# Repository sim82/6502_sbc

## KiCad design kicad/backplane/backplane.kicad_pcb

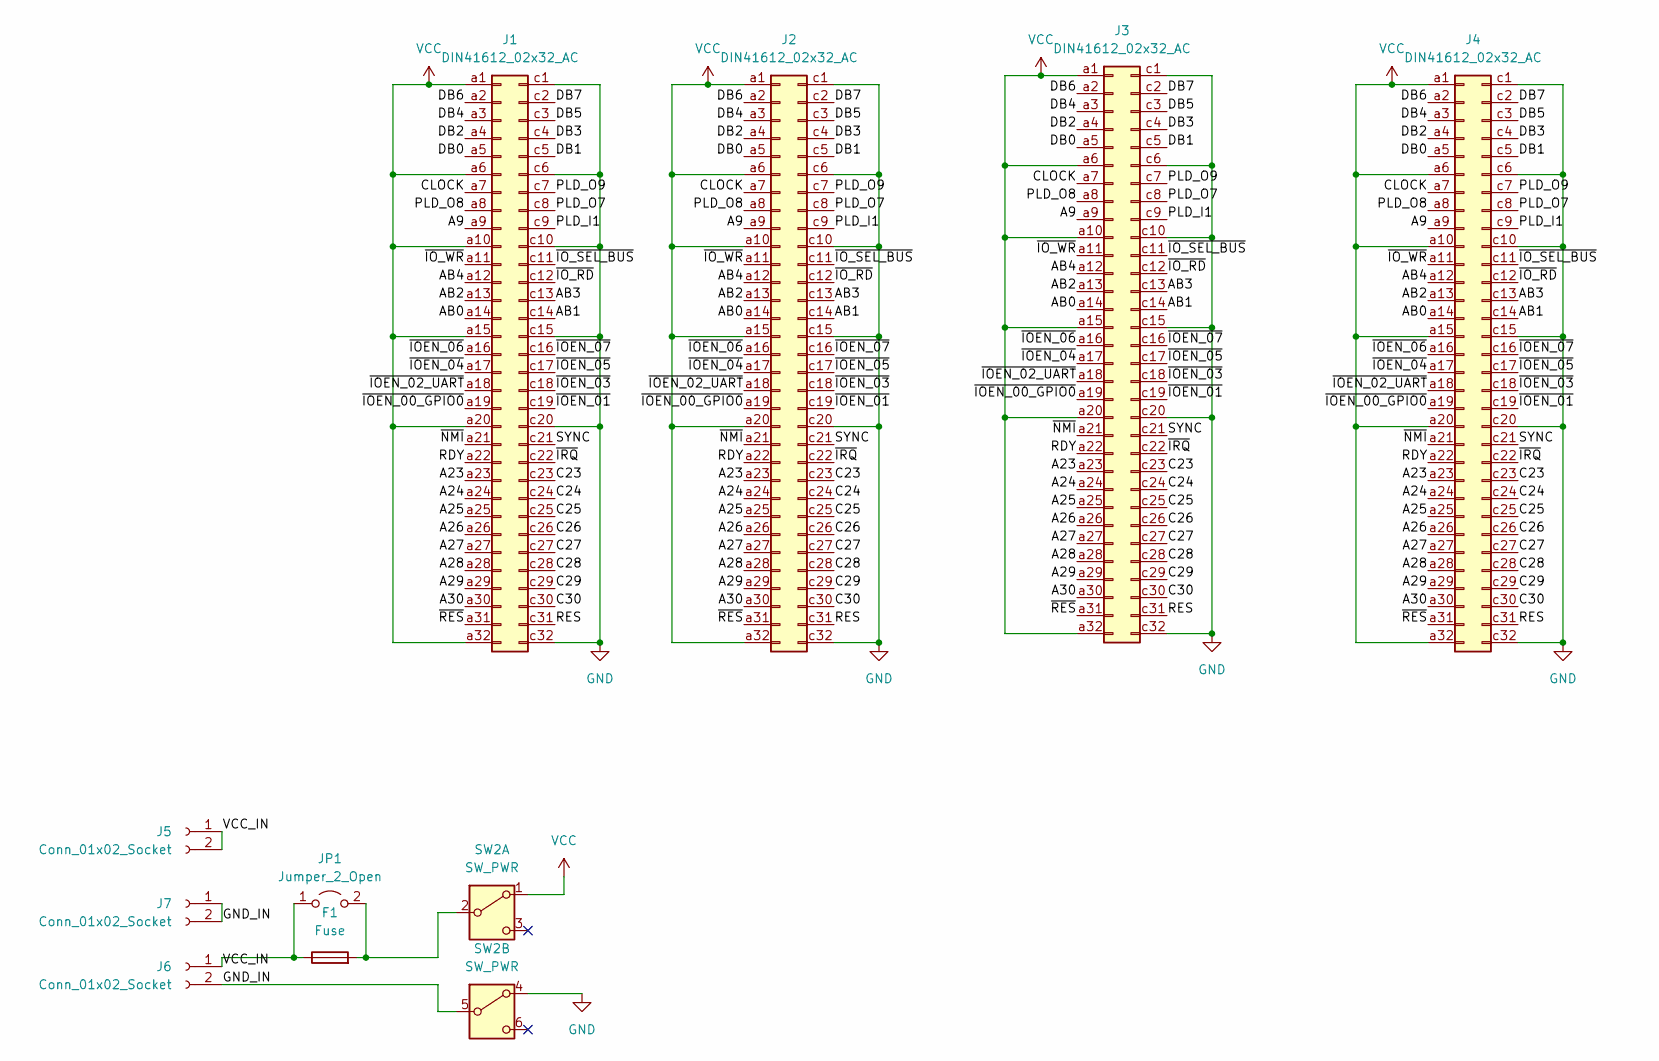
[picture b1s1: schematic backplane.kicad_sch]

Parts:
F1: Fuse; Fuseholder_Cylinder-5x20mm_Stelvio-Kontek_PTF78_Horizontal_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
J1, J2, J3, J4: DIN41612_02x32_AC; DIN41612_C_2x32_Female_Vertical_THT
J5, J6, J7: Conn_01x02_Socket; PinSocket_1x02_P2.54mm_Vertical
JP1: Jumper_2_Open; TestPoint_2Pads_Pitch2.54mm_Drill0.8mm
SW2: SW_PWR; 7x7DPDT

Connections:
/A9: J1.a9, J2.a9, J3.a9, J4.a9
/A23: J1.a23, J2.a23, J3.a23, J4.a23
/A24: J1.a24, J2.a24, J3.a24, J4.a24
/A25: J1.a25, J2.a25, J3.a25, J4.a25
/A26: J1.a26, J2.a26, J3.a26, J4.a26
/A27: J1.a27, J2.a27, J3.a27, J4.a27
/A28: J1.a28, J2.a28, J3.a28, J4.a28
/A29: J1.a29, J2.a29, J3.a29, J4.a29
/A30: J1.a30, J2.a30, J3.a30, J4.a30
/AB0: J1.a14, J2.a14, J3.a14, J4.a14
/AB1: J1.c14, J2.c14, J3.c14, J4.c14
/AB2: J1.a13, J2.a13, J3.a13, J4.a13
/AB3: J1.c13, J2.c13, J3.c13, J4.c13
/AB4: J1.a12, J2.a12, J3.a12, J4.a12
/C23: J1.c23, J2.c23, J3.c23, J4.c23
/C24: J1.c24, J2.c24, J3.c24, J4.c24
/C25: J1.c25, J2.c25, J3.c25, J4.c25
/C26: J1.c26, J2.c26, J3.c26, J4.c26
/C27: J1.c27, J2.c27, J3.c27, J4.c27
/C28: J1.c28, J2.c28, J3.c28, J4.c28
/C29: J1.c29, J2.c29, J3.c29, J4.c29
/C30: J1.c30, J2.c30, J3.c30, J4.c30
/CLOCK: J1.a7, J2.a7, J3.a7, J4.a7
/DB0: J1.a5, J2.a5, J3.a5, J4.a5
/DB1: J1.c5, J2.c5, J3.c5, J4.c5
/DB2: J1.a4, J2.a4, J3.a4, J4.a4
/DB3: J1.c4, J2.c4, J3.c4, J4.c4
/DB4: J1.a3, J2.a3, J3.a3, J4.a3
/DB5: J1.c3, J2.c3, J3.c3, J4.c3
/DB6: J1.a2, J2.a2, J3.a2, J4.a2
/DB7: J1.c2, J2.c2, J3.c2, J4.c2
/GND_IN: J6.2, J7.1, J7.2, SW2.5 (B)
/PLD_I1: J1.c9, J2.c9, J3.c9, J4.c9
/PLD_O7: J1.c8, J2.c8, J3.c8, J4.c8
/PLD_O8: J1.a8, J2.a8, J3.a8, J4.a8
/PLD_O9: J1.c7, J2.c7, J3.c7, J4.c7
/RDY: J1.a22, J2.a22, J3.a22, J4.a22
/RES: J1.c31, J2.c31, J3.c31, J4.c31
/SYNC: J1.c21, J2.c21, J3.c21, J4.c21
/VCC_IN: F1.1, J5.1, J5.2, J6.1, JP1.1 (A)
/~IOEN_00_GPIO0: J1.a19, J2.a19, J3.a19, J4.a19
/~IOEN_01: J1.c19, J2.c19, J3.c19, J4.c19
/~IOEN_02_UART: J1.a18, J2.a18, J3.a18, J4.a18
/~IOEN_03: J1.c18, J2.c18, J3.c18, J4.c18
/~IOEN_04: J1.a17, J2.a17, J3.a17, J4.a17
/~IOEN_05: J1.c17, J2.c17, J3.c17, J4.c17
/~IOEN_06: J1.a16, J2.a16, J3.a16, J4.a16
/~IOEN_07: J1.c16, J2.c16, J3.c16, J4.c16
/~IO_RD: J1.c12, J2.c12, J3.c12, J4.c12
/~IO_SEL_BUS: J1.c11, J2.c11, J3.c11, J4.c11
/~IO_WR: J1.a11, J2.a11, J3.a11, J4.a11
/~IRQ: J1.c22, J2.c22, J3.c22, J4.c22
/~NMI: J1.a21, J2.a21, J3.a21, J4.a21
/~RES: J1.a31, J2.a31, J3.a31, J4.a31
GND: J1.c1, J1.c6, J1.c10, J1.c15, J1.c20, J1.c32, J2.c1, J2.c6, J2.c10, J2.c15, J2.c20, J2.c32, J3.c1, J3.c6, J3.c10, J3.c15, J3.c20, J3.c32, J4.c1, J4.c6, J4.c10, J4.c15, J4.c20, J4.c32, SW2.4 (A)
unnamed: F1.2, JP1.2 (B), SW2.2 (B)
VCC: J1.a1, J1.a6, J1.a10, J1.a15, J1.a20, J1.a32, J2.a1, J2.a6, J2.a10, J2.a15, J2.a20, J2.a32, J3.a1, J3.a6, J3.a10, J3.a15, J3.a20, J3.a32, J4.a1, J4.a6, J4.a10, J4.a15, J4.a20, J4.a32, SW2.1 (A)

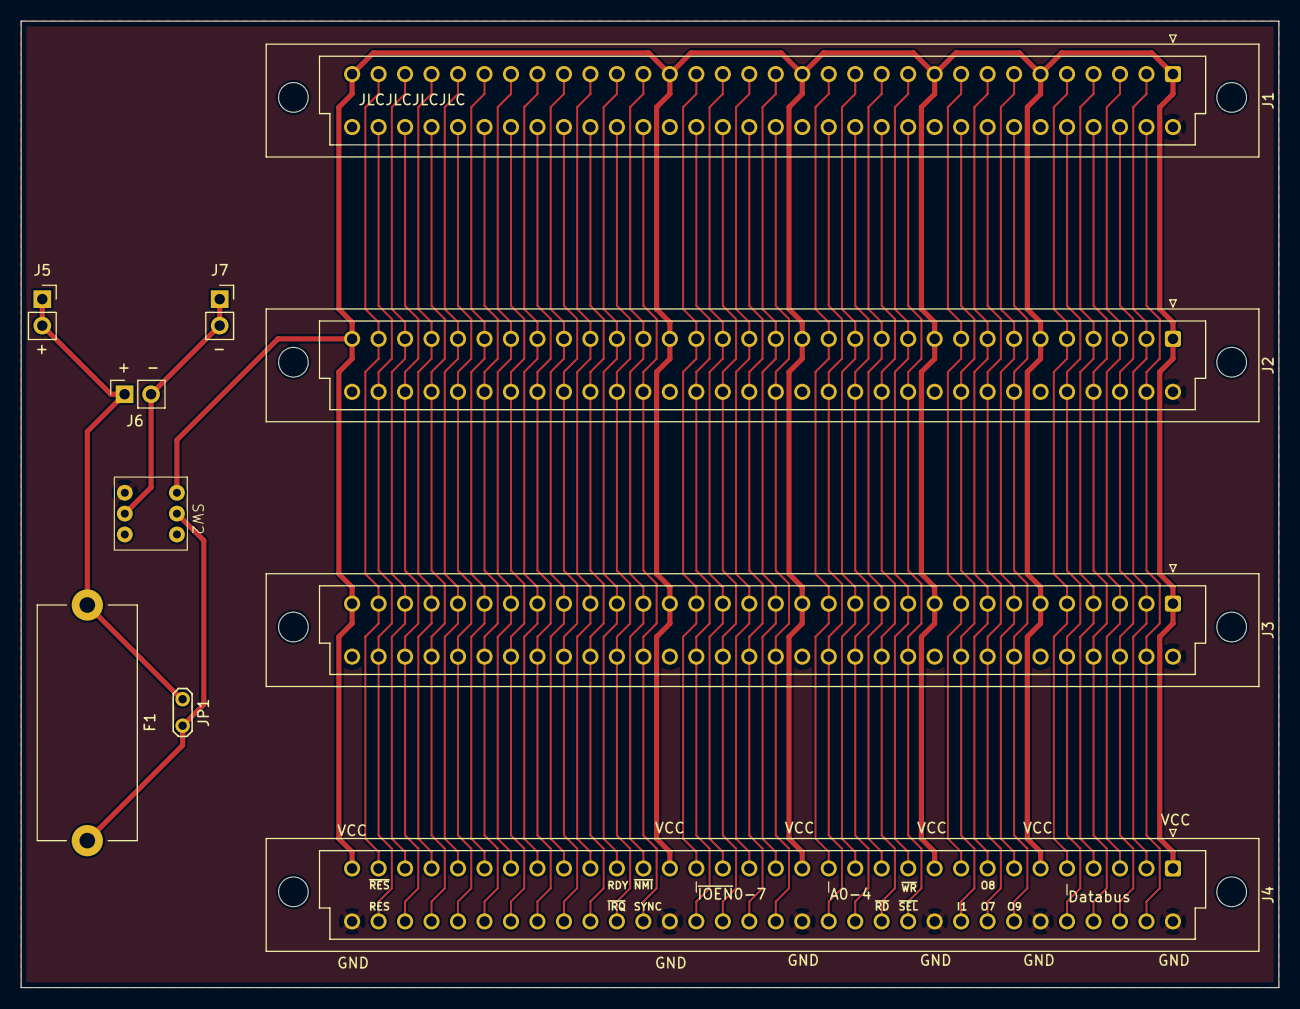
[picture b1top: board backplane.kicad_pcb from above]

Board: 2 copper layers, 120.6 x 92.7 mm, 10 parts (0 on the bottom side), 57 nets.

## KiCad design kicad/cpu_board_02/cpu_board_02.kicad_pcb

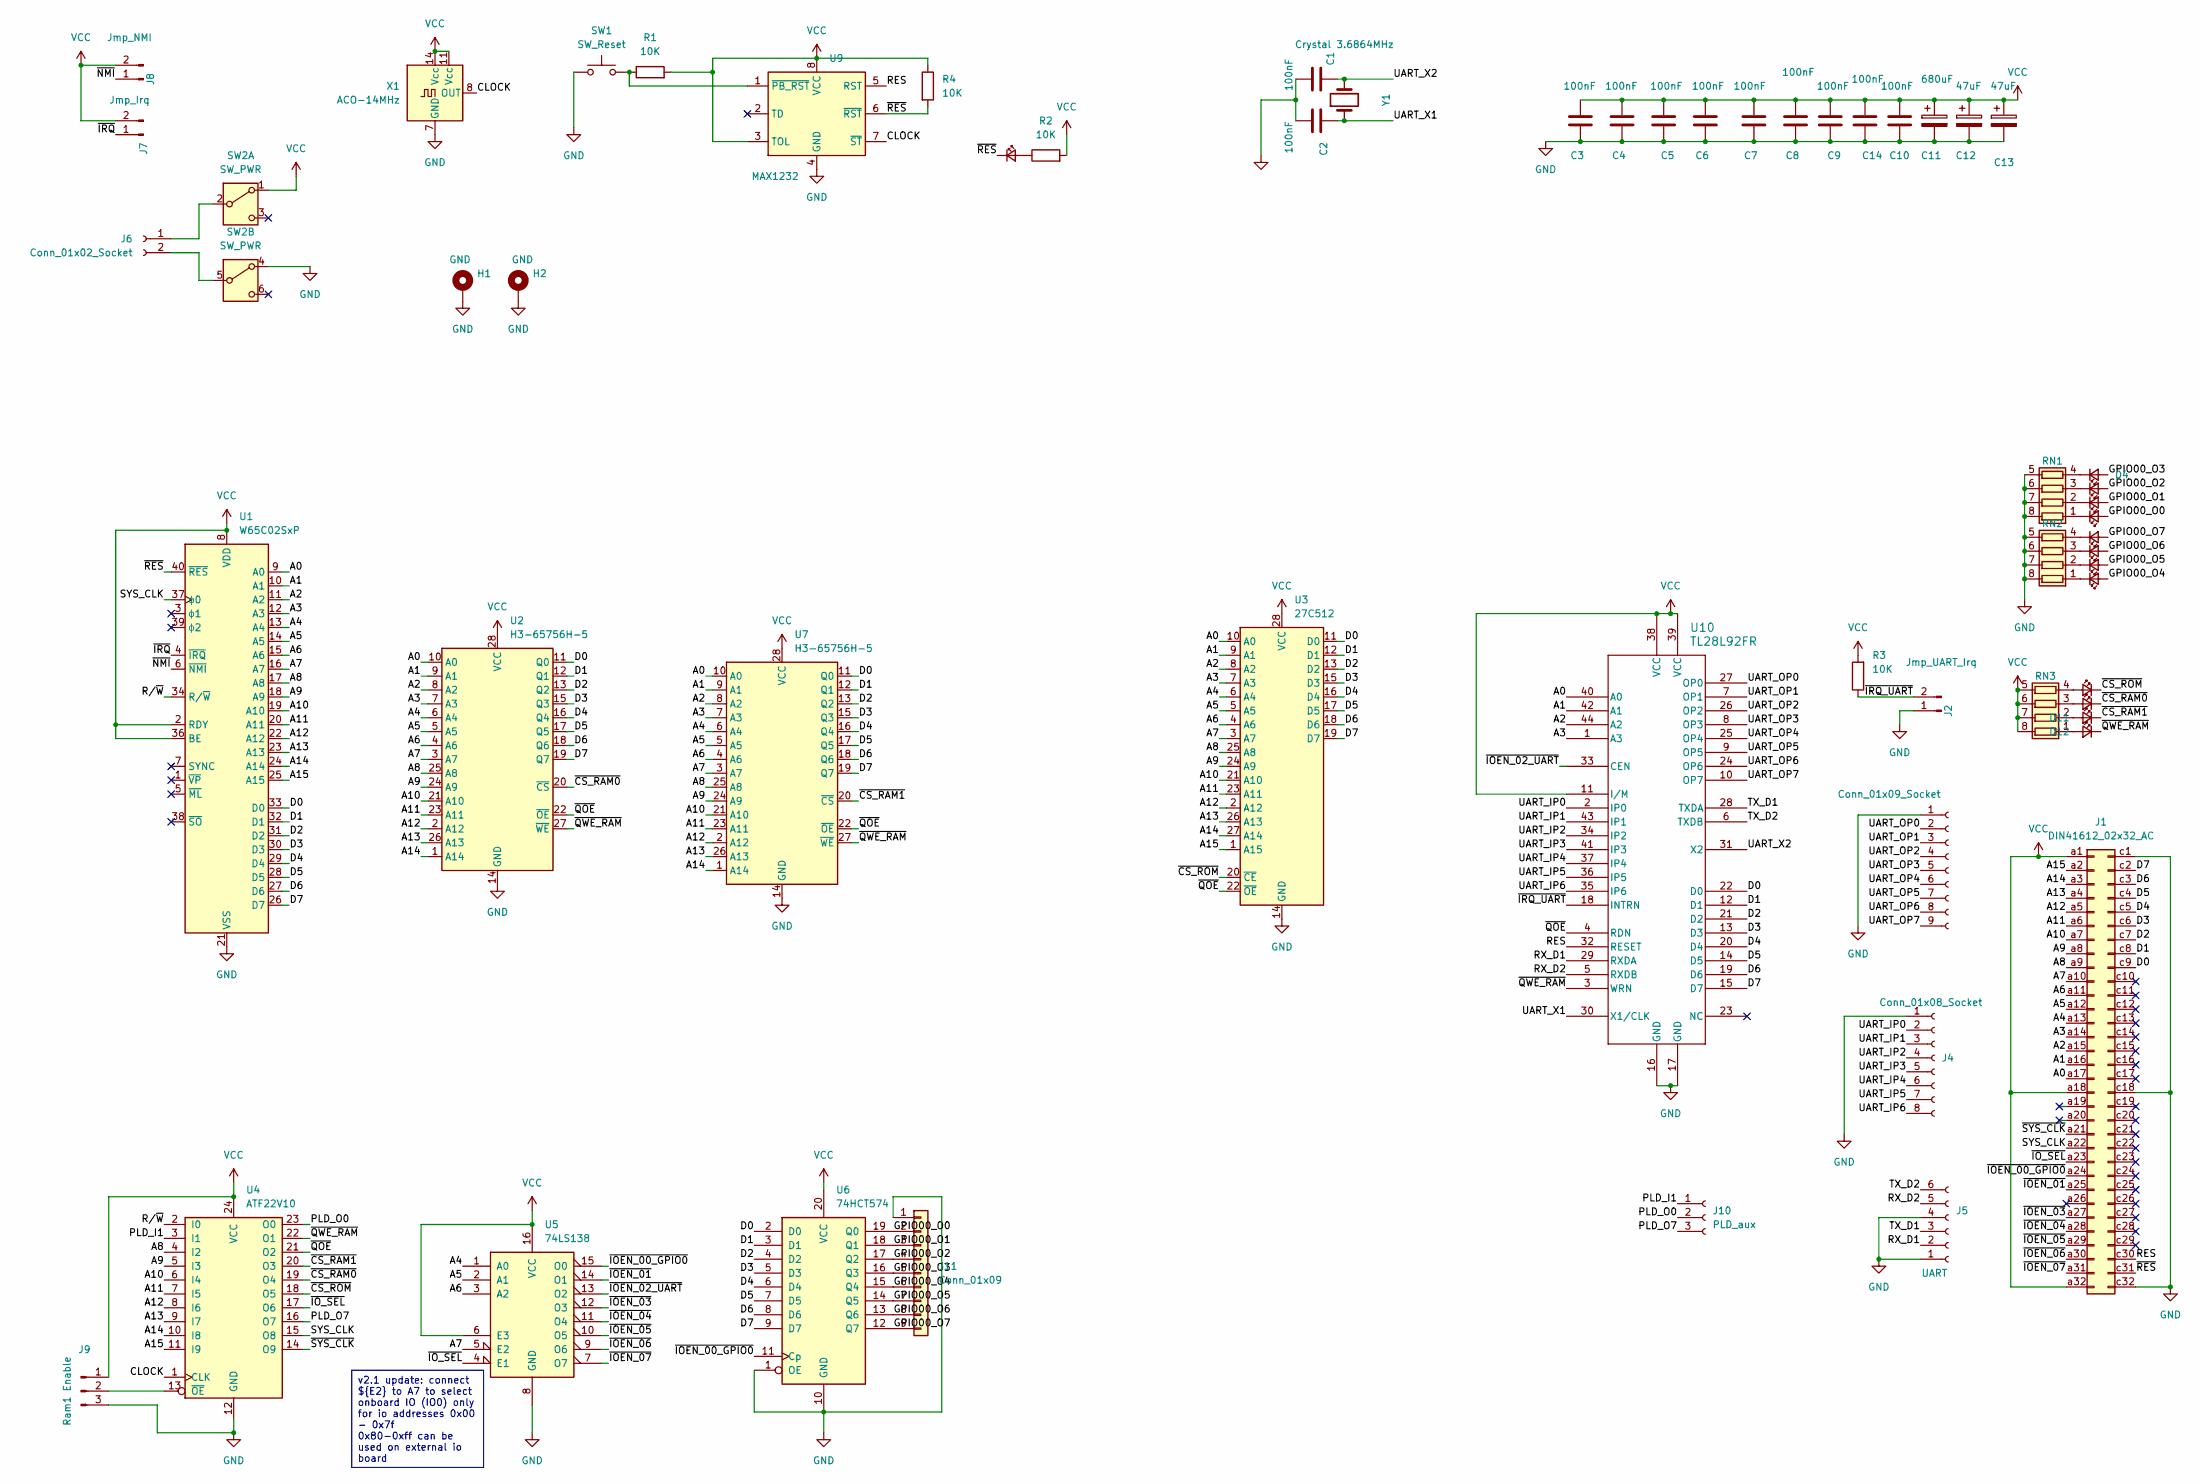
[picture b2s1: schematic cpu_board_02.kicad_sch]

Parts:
C1, C2: 100nF; C_Disc_D4.7mm_W2.5mm_P5.00mm
C3, C4, C5, C6, C7, C8, C9, C10, C14: 100nF; C_0805_2012Metric_Pad1.18x1.45mm_HandSolder
C11: 680uF; CP_Radial_D8.0mm_P5.00mm
C12, C13: 47uF; CP_Radial_D4.0mm_P2.00mm
D1, D2, D3, D4, D5, D6, D7, D8, D9, D10, D11, D12, D13: LED_Small; LED_0805_2012Metric_Pad1.15x1.40mm_HandSolder
H1, H2: GND; MountingHole_3.2mm_M3_DIN965_Pad
J1: DIN41612_02x32_AC; DIN41612_C_2x32_Male_Horizontal_THT
J2: Jmp_UART_Irq; PinSocket_1x02_P2.54mm_Vertical
J3: Conn_01x09_Socket; PinSocket_1x09_P2.54mm_Vertical
J4: Conn_01x08_Socket; PinSocket_1x08_P2.54mm_Vertical
J5: UART; PinSocket_1x06_P2.54mm_Vertical
J6: Conn_01x02_Socket; PinSocket_1x02_P2.54mm_Vertical
J7: Jmp_Irq; PinHeader_1x02_P2.54mm_Vertical
J8: Jmp_NMI; PinHeader_1x02_P2.54mm_Vertical
J9: Ram1 Enable; PinHeader_1x03_P2.54mm_Vertical
J10: PLD_aux; PinSocket_1x03_P2.54mm_Vertical
J11: Conn_01x09; PinSocket_1x09_P2.54mm_Vertical
R1, R2, R3, R4: 10K; R_0805_2012Metric_Pad1.20x1.40mm_HandSolder
RN1, RN2, RN3: R_Pack04; R_Array_Convex_4x0612
SW1: SW_Reset; SW_TH_Tactile_Omron_B3F-10xx
SW2: SW_PWR; 7x7DPDT
U1: W65C02SxP; DIP-40_W15.24mm_Socket
U2, U7: H3-65756H-5; DIP-28_W7.62mm_Socket
U3: 27C512; DIP-28_W15.24mm_Socket
U4: ATF22V10; DIP-24_W7.62mm_Socket
U5: 74LS138; DIP-16_W7.62mm_Socket
U6: 74HCT574; DIP-20_W7.62mm_Socket
U9: MAX1232; SO-8_3.9x4.9mm_P1.27mm
U10: TL28L92FR; MQFP-44_10x10mm_P0.8mm
X1: ACO-14MHz; DIP-14_W7.62mm
Y1: Crystal 3.6864MHz; Crystal_HC49-4H_Vertical

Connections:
/A0: J1.a17, U1.9 (A0), U2.10 (A0), U3.10 (A0), U7.10 (A0), U10.40 (A0)
/A1: J1.a16, U1.10 (A1), U2.9 (A1), U3.9 (A1), U7.9 (A1), U10.42 (A1)
/A2: J1.a15, U1.11 (A2), U2.8 (A2), U3.8 (A2), U7.8 (A2), U10.44 (A2)
/A3: J1.a14, U1.12 (A3), U2.7 (A3), U3.7 (A3), U7.7 (A3), U10.1 (A3)
/A4: J1.a13, U1.13 (A4), U2.6 (A4), U3.6 (A4), U5.1 (A0), U7.6 (A4)
/A5: J1.a12, U1.14 (A5), U2.5 (A5), U3.5 (A5), U5.2 (A1), U7.5 (A5)
/A6: J1.a11, U1.15 (A6), U2.4 (A6), U3.4 (A6), U5.3 (A2), U7.4 (A6)
/A7: J1.a10, U1.16 (A7), U2.3 (A7), U3.3 (A7), U5.5 (E2), U7.3 (A7)
/A8: J1.a9, U1.17 (A8), U2.25 (A8), U3.25 (A8), U4.4 (I2), U7.25 (A8)
/A9: J1.a8, U1.18 (A9), U2.24 (A9), U3.24 (A9), U4.5 (I3), U7.24 (A9)
/A10: J1.a7, U1.19 (A10), U2.21 (A10), U3.21 (A10), U4.6 (I4), U7.21 (A10)
/A11: J1.a6, U1.20 (A11), U2.23 (A11), U3.23 (A11), U4.7 (I5), U7.23 (A11)
/A12: J1.a5, U1.22 (A12), U2.2 (A12), U3.2 (A12), U4.8 (I6), U7.2 (A12)
/A13: J1.a4, U1.23 (A13), U2.26 (A13), U3.26 (A13), U4.9 (I7), U7.26 (A13)
/A14: J1.a3, U1.24 (A14), U2.1 (A14), U3.27 (A14), U4.10 (I8), U7.1 (A14)
/A15: J1.a2, U1.25 (A15), U3.1 (A15), U4.11 (I9)
/CLOCK: U4.1 (CLK), U9.7 (~ST), X1.8 (OUT)
/D0: J1.c9, U1.33 (D0), U2.11 (Q0), U3.11 (D0), U6.2 (D0), U7.11 (Q0), U10.22 (D0)
/D1: J1.c8, U1.32 (D1), U2.12 (Q1), U3.12 (D1), U6.3 (D1), U7.12 (Q1), U10.12 (D1)
/D2: J1.c7, U1.31 (D2), U2.13 (Q2), U3.13 (D2), U6.4 (D2), U7.13 (Q2), U10.21 (D2)
/D3: J1.c6, U1.30 (D3), U2.15 (Q3), U3.15 (D3), U6.5 (D3), U7.15 (Q3), U10.13 (D3)
/D4: J1.c5, U1.29 (D4), U2.16 (Q4), U3.16 (D4), U6.6 (D4), U7.16 (Q4), U10.20 (D4)
/D5: J1.c4, U1.28 (D5), U2.17 (Q5), U3.17 (D5), U6.7 (D5), U7.17 (Q5), U10.14 (D5)
/D6: J1.c3, U1.27 (D6), U2.18 (Q6), U3.18 (D6), U6.8 (D6), U7.18 (Q6), U10.19 (D6)
/D7: J1.c2, U1.26 (D7), U2.19 (Q7), U3.19 (D7), U6.9 (D7), U7.19 (Q7), U10.15 (D7)
/GPIO00_O0: D1.2 (A), J11.2, U6.19 (Q0)
/GPIO00_O1: D2.2 (A), J11.3, U6.18 (Q1)
/GPIO00_O2: D3.2 (A), J11.4, U6.17 (Q2)
/GPIO00_O3: D4.2 (A), J11.5, U6.16 (Q3)
/GPIO00_O4: D5.2 (A), J11.6, U6.15 (Q4)
/GPIO00_O5: D6.2 (A), J11.7, U6.14 (Q5)
/GPIO00_O6: D7.2 (A), J11.8, U6.13 (Q6)
/GPIO00_O7: D8.2 (A), J11.9, U6.12 (Q7)
/PLD_I1: J10.1, U4.3 (I1)
/PLD_O0: J10.2, U4.23 (O0)
/PLD_O7: J10.3, U4.16 (O7)
/RES: J1.c30, U9.5 (RST), U10.32 (RESET)
/RX_D1: J5.2, U10.29 (RXDA)
/RX_D2: J5.5, U10.5 (RXDB)
/R/~W: U1.34 (R/~W), U4.2 (I0)
/SYS_CLK: J1.a22, U1.37 (ϕ0), U4.15 (O8)
/TX_D1: J5.3, U10.28 (TXDA)
/TX_D2: J5.6, U10.6 (TXDB)
/UART_IP0: J4.2, U10.2 (IP0)
/UART_IP1: J4.3, U10.43 (IP1)
/UART_IP2: J4.4, U10.34 (IP2)
/UART_IP3: J4.5, U10.41 (IP3)
/UART_IP4: J4.6, U10.37 (IP4)
/UART_IP5: J4.7, U10.36 (IP5)
/UART_IP6: J4.8, U10.35 (IP6)
/UART_OP0: J3.2, U10.27 (OP0)
/UART_OP1: J3.3, U10.7 (OP1)
/UART_OP2: J3.4, U10.26 (OP2)
/UART_OP3: J3.5, U10.8 (OP3)
/UART_OP4: J3.6, U10.25 (OP4)
/UART_OP5: J3.7, U10.9 (OP5)
/UART_OP6: J3.8, U10.24 (OP6)
/UART_OP7: J3.9, U10.10 (OP7)
/UART_X1: C2.1, U10.30 (X1/CLK), Y1.1
/UART_X2: C1.1, U10.31 (X2), Y1.2
/~CS_RAM0: D10.1 (K), U2.20 (~CS), U4.19 (O4)
/~CS_RAM1: D11.1 (K), U4.20 (O3), U7.20 (~CS)
/~CS_ROM: D9.1 (K), U3.20 (~CE), U4.18 (O5)
/~IOEN_00_GPIO0: J1.a24, U5.15 (O0), U6.11 (Cp)
/~IOEN_01: J1.a25, U5.14 (O1)
/~IOEN_02_UART: U5.13 (O2), U10.33 (CEN)
/~IOEN_03: J1.a27, U5.12 (O3)
/~IOEN_04: J1.a28, U5.11 (O4)
/~IOEN_05: J1.a29, U5.10 (O5)
/~IOEN_06: J1.a30, U5.9 (O6)
/~IOEN_07: J1.a31, U5.7 (O7)
/~IO_SEL: J1.a23, U4.17 (O6), U5.4 (E1)
/~IRQ_UART: J2.2, R3.1, U10.18 (INTRN)
/~IRQ: J7.1, U1.4 (~IRQ)
/~NMI: J8.1, U1.6 (~NMI)
/~QOE: U2.22 (~OE), U3.22 (~OE), U4.21 (O2), U7.22 (~OE), U10.4 (RDN)
/~QWE_RAM: D12.1 (K), U2.27 (~WE), U4.22 (O1), U7.27 (~WE), U10.3 (WRN)
/~RES: D13.1 (K), J1.c31, R4.2, U1.40 (~RES), U9.6 (~RST)
/~SYS_CLK: J1.a21, U4.14 (O9)
GND: C1.2, C2.2, C3.2, C4.2, C5.2, C6.2, C7.2, C8.2, C9.2, C10.2, C11.2, C12.2, C13.2, C14.2, H1.1, H2.1, J1.c1, J1.c18, J1.c32, J2.1, J3.1, J4.1, J5.1, J5.4, J9.3, J11.1, RN1.5 (R4.2), RN1.6 (R3.2), RN1.7 (R2.2), RN1.8 (R1.2), RN2.5 (R4.2), RN2.6 (R3.2), RN2.7 (R2.2), RN2.8 (R1.2), SW1.2, SW2.4 (A), U1.21 (VSS), U2.14 (GND), U3.14 (GND), U4.12 (GND), U5.8 (GND), U6.1 (OE), U6.10 (GND), U7.14 (GND), U9.4 (GND), U10.16 (GND), U10.17 (GND), X1.7 (GND)
unnamed: D1.1 (K), RN1.1 (R1.1)
unnamed: D2.1 (K), RN1.2 (R2.1)
unnamed: D3.1 (K), RN1.3 (R3.1)
unnamed: D4.1 (K), RN1.4 (R4.1)
unnamed: D5.1 (K), RN2.1 (R1.1)
unnamed: D6.1 (K), RN2.2 (R2.1)
unnamed: D7.1 (K), RN2.3 (R3.1)
unnamed: D8.1 (K), RN2.4 (R4.1)
unnamed: D9.2 (A), RN3.4 (R4.1)
unnamed: D10.2 (A), RN3.3 (R3.1)
unnamed: D11.2 (A), RN3.2 (R2.1)
unnamed: D12.2 (A), RN3.1 (R1.1)
unnamed: D13.2 (A), R2.1
unnamed: J6.1, SW2.2 (B)
unnamed: J6.2, SW2.5 (B)
unnamed: J9.2, U4.13 (~OE)
unnamed: R1.1, SW1.1, U9.1 (~PB_RST)
VCC: C3.1, C4.1, C5.1, C6.1, C7.1, C8.1, C9.1, C10.1, C11.1, C12.1, C13.1, C14.1, J1.a1, J1.a18, J1.a32, J7.2, J8.2, J9.1, R1.2, R2.2, R3.2, R4.1, RN3.5 (R4.2), RN3.6 (R3.2), RN3.7 (R2.2), RN3.8 (R1.2), SW2.1 (A), U1.2 (RDY), U1.8 (VDD), U1.36 (BE), U2.28 (VCC), U3.28 (VCC), U4.24 (VCC), U5.6 (E3), U5.16 (VCC), U6.20 (VCC), U7.28 (VCC), U9.3 (TOL), U9.8 (VCC), U10.11 (I/M), U10.38 (VCC), U10.39 (VCC), X1.11 (Vcc), X1.14 (Vcc)

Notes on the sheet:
v2.1 update: connect ${E2} to A7 to select onboard IO (IO0) only for io addresses 0x00 - 0x7f 0x80-0xff can be used on external io board

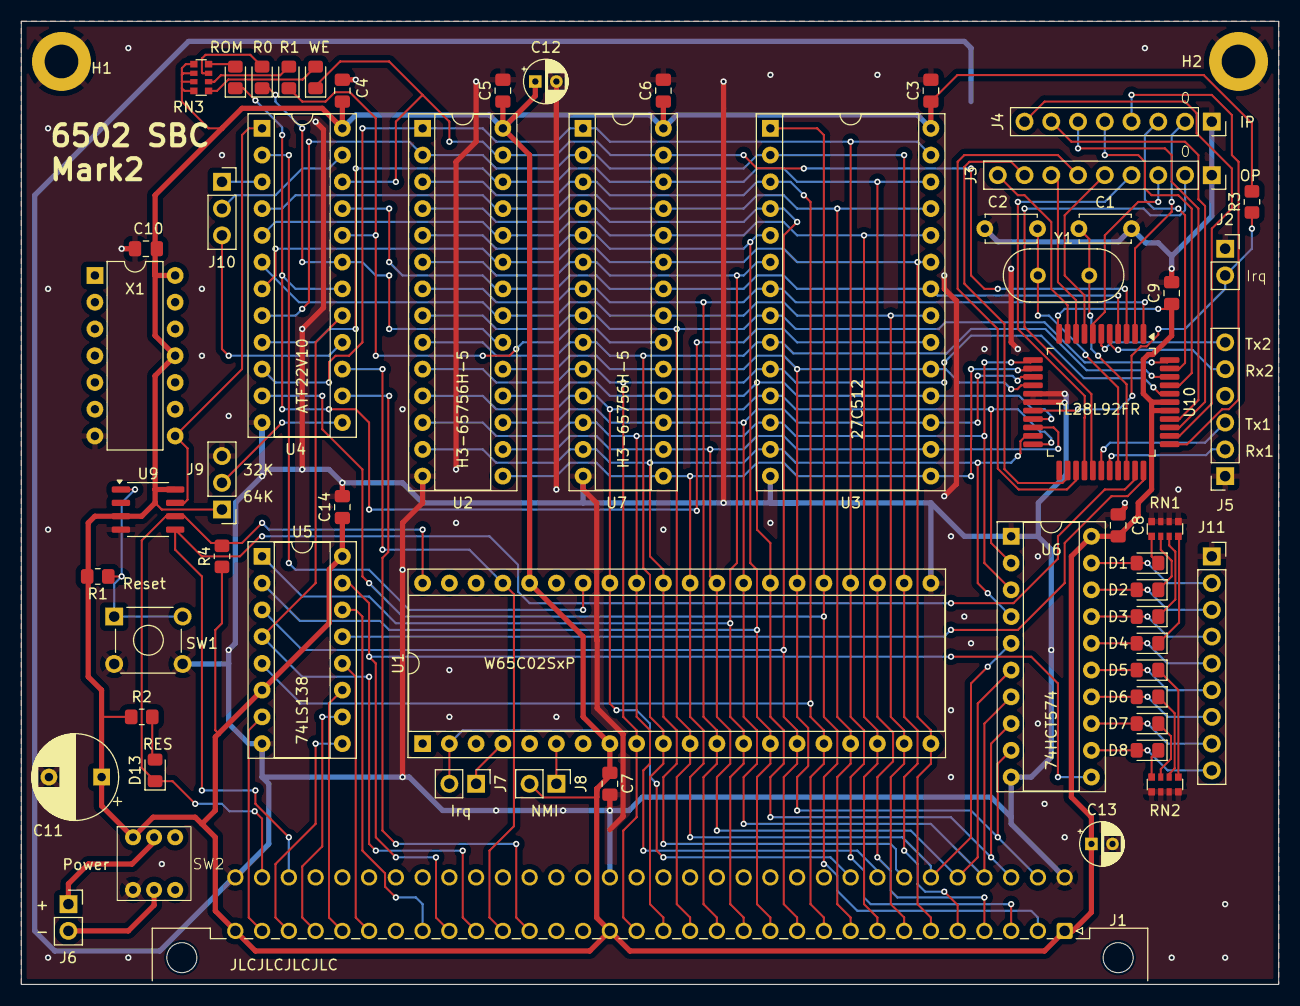
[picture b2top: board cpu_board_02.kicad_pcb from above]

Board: 2 copper layers, 119.4 x 91.4 mm, 60 parts (0 on the bottom side), 98 nets.

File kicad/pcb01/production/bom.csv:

Designator,Footprint,Quantity,Value,LCSC Part #
"C1, C2",C_Disc_D4.7mm_W2.5mm_P5.00mm,2,100nF,
"C10, C14, C3, C4, C5, C6, C7, C8, C9",0805,9,100nF,
C11,CP_Radial_D8.0mm_P5.00mm,1,680uF,
"C12, C13",CP_Radial_D4.0mm_P2.00mm,2,47uF,
"D1, D10, D11, D12, D13, D2, D3, D4, D5, D6, D7, D8, D9",0805,13,LED_Small,
"H1, H2",MountingHole_3.2mm_M3_DIN965_Pad,2,GND,
J1,DIN41612_C_2x32_Male_Horizontal_THT,1,DIN41612_02x32_AC,
J10,PinSocket_1x03_P2.54mm_Vertical,1,PLD_aux,
J11,PinSocket_1x09_P2.54mm_Vertical,1,Conn_01x09,
J2,PinSocket_1x02_P2.54mm_Vertical,1,Jmp_UART_Irq,
J3,PinSocket_1x09_P2.54mm_Vertical,1,Conn_01x09_Socket,
J4,PinSocket_1x08_P2.54mm_Vertical,1,Conn_01x08_Socket,
J5,PinSocket_1x06_P2.54mm_Vertical,1,UART,
J6,PinSocket_1x02_P2.54mm_Vertical,1,Conn_01x02_Socket,
J7,PinHeader_1x02_P2.54mm_Vertical,1,Jmp_Irq,
J8,PinHeader_1x02_P2.54mm_Vertical,1,Jmp_NMI,
J9,PinHeader_1x03_P2.54mm_Vertical,1,Ram1 Enable,
"R1, R2, R3, R4",0805,4,10K,
"RN1, RN2, RN3",R_Array_Convex_4x0612,3,R_Pack04,
SW1,SW_TH_Tactile_Omron_B3F-10xx,1,SW_Reset,
SW2,7x7DPDT,1,SW_PWR,
U1,DIP-40_W15.24mm_Socket,1,W65C02SxP,
U10,MQFP-44_10x10mm_P0.8mm,1,TL28L92FR,
"U2, U7",DIP-28_W7.62mm_Socket,2,H3-65756H-5,
U3,DIP-28_W15.24mm_Socket,1,27C512,
U4,DIP-24_W7.62mm_Socket,1,ATF22V10,
U5,DIP-16_W7.62mm_Socket,1,74LS138,
U6,DIP-20_W7.62mm_Socket,1,74HCT574,
U9,SO-8_3.9x4.9mm_P1.27mm,1,MAX1232,
X1,DIP-14_W7.62mm,1,ACO-14MHz,
Y1,Crystal_HC49-4H_Vertical,1,Crystal 3.6864MHz,

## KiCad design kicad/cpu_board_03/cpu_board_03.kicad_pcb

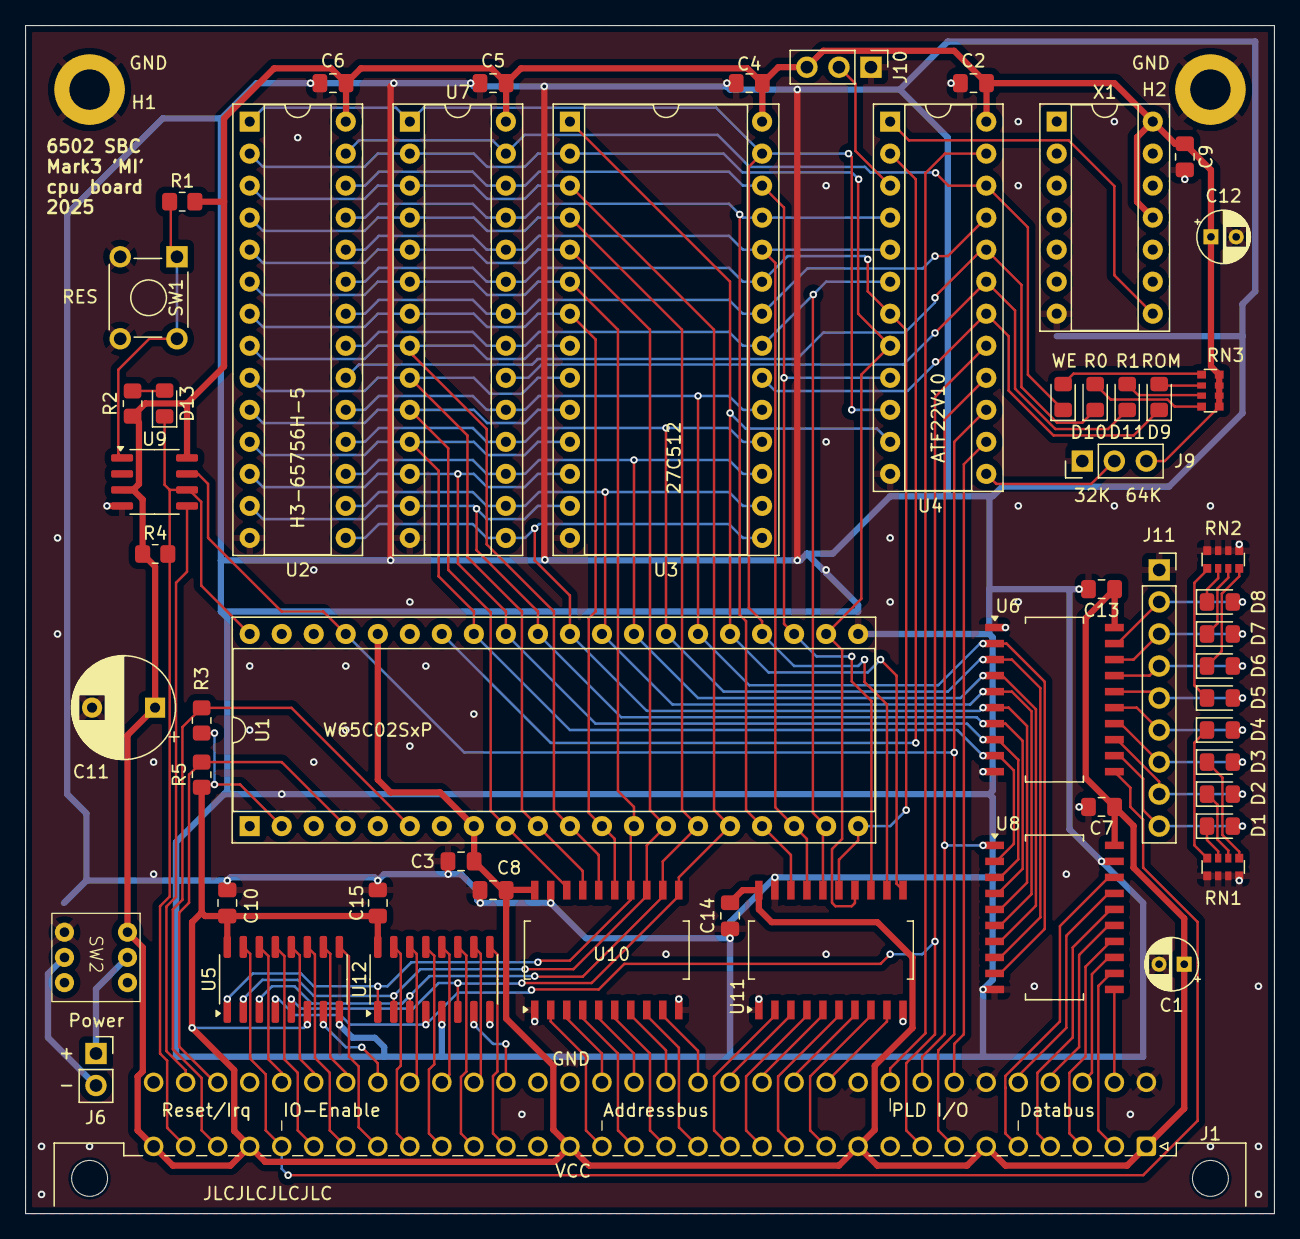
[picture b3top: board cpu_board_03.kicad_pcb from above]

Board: 2 copper layers, 99.1 x 94.2 mm, 58 parts (0 on the bottom side), 108 nets.

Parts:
C1, C12: 47uF; CP_Radial_D4.0mm_P2.00mm
C2, C3, C4, C5, C6, C7, C8, C9, C10, C13, C14, C15: 100nF; C_0805_2012Metric_Pad1.18x1.45mm_HandSolder
C11: 680uF; CP_Radial_D8.0mm_P5.00mm
D1, D2, D3, D4, D5, D6, D7, D8, D9, D10, D11, D12, D13: LED_Small; LED_0805_2012Metric_Pad1.15x1.40mm_HandSolder
H1, H2: GND; MountingHole_3.2mm_M3_DIN965_Pad
J1: DIN41612_02x32_AC; DIN41612_C_2x32_Male_Horizontal_THT
J6: Conn_01x02_Socket; PinSocket_1x02_P2.54mm_Vertical
J9: Ram1 Enable; PinHeader_1x03_P2.54mm_Vertical
J10: PLD_aux; PinHeader_1x03_P2.54mm_Vertical
J11: Conn_01x09; PinSocket_1x09_P2.54mm_Vertical
R1, R2, R3, R4, R5: 10K; R_0805_2012Metric_Pad1.20x1.40mm_HandSolder
RN1, RN2, RN3: R_Pack04; R_Array_Convex_4x0612
SW1: SW_Reset; SW_TH_Tactile_Omron_B3F-10xx
SW2: SW_PWR; 7x7DPDT
U1: W65C02SxP; DIP-40_W15.24mm_Socket
U2, U7: H3-65756H-5; DIP-28_W7.62mm_Socket
U3: 27C512; DIP-28_W15.24mm_Socket
U4: ATF22V10; DIP-24_W7.62mm_Socket
U5, U12: 74LS138; SO-16_3.9x9.9mm_P1.27mm
U6: 74HCT574; SO-20_12.8x7.5mm_P1.27mm
U8, U10, U11: 74HC245; SO-20_12.8x7.5mm_P1.27mm
U9: MAX1232; SO-8_3.9x4.9mm_P1.27mm
X1: ACO-14MHz; DIP-14_W7.62mm_Socket

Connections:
/A0: U1.9 (A0), U2.10 (A0), U3.10 (A0), U7.10 (A0), U10.18 (B0)
/A1: U1.10 (A1), U2.9 (A1), U3.9 (A1), U7.9 (A1), U10.17 (B1)
/A2: U1.11 (A2), U2.8 (A2), U3.8 (A2), U7.8 (A2), U10.16 (B2)
/A3: U1.12 (A3), U2.7 (A3), U3.7 (A3), U7.7 (A3), U10.15 (B3)
/A4: U1.13 (A4), U2.6 (A4), U3.6 (A4), U5.1 (A0), U7.6 (A4), U10.14 (B4), U12.1 (A0)
/A5: U1.14 (A5), U2.5 (A5), U3.5 (A5), U5.2 (A1), U7.5 (A5), U10.13 (B5), U12.2 (A1)
/A6: U1.15 (A6), U2.4 (A6), U3.4 (A6), U5.3 (A2), U7.4 (A6), U10.12 (B6), U12.3 (A2)
/A7: U1.16 (A7), U2.3 (A7), U3.3 (A7), U5.5 (E2), U7.3 (A7), U10.11 (B7), U12.6 (E3)
/A8: U1.17 (A8), U2.25 (A8), U3.25 (A8), U4.4 (I2), U7.25 (A8), U11.18 (B0)
/A9: U1.18 (A9), U2.24 (A9), U3.24 (A9), U4.5 (I3), U7.24 (A9), U11.17 (B1)
/A10: U1.19 (A10), U2.21 (A10), U3.21 (A10), U4.6 (I4), U7.21 (A10), U11.16 (B2)
/A11: U1.20 (A11), U2.23 (A11), U3.23 (A11), U4.7 (I5), U7.23 (A11), U11.15 (B3)
/A12: U1.22 (A12), U2.2 (A12), U3.2 (A12), U4.8 (I6), U7.2 (A12), U11.14 (B4)
/A13: U1.23 (A13), U2.26 (A13), U3.26 (A13), U4.9 (I7), U7.26 (A13), U11.13 (B5)
/A14: U1.24 (A14), U2.1 (A14), U3.27 (A14), U4.10 (I8), U7.1 (A14), U11.12 (B6)
/A15: U1.25 (A15), U3.1 (A15), U4.11 (I9), U11.11 (B7)
/AB0: J1.a18, U10.2 (A0)
/AB1: J1.c18, U10.3 (A1)
/AB2: J1.a17, U10.4 (A2)
/AB3: J1.c17, U10.5 (A3)
/AB4: J1.a16, U10.6 (A4)
/AB5: J1.c16, U10.7 (A5)
/AB6: J1.a15, U10.8 (A6)
/AB7: J1.c15, U10.9 (A7)
/AB8: J1.a14, U11.2 (A0)
/AB9: J1.c14, U11.3 (A1)
/AB10: J1.a13, U11.4 (A2)
/AB11: J1.c13, U11.5 (A3)
/AB12: J1.a12, U11.6 (A4)
/AB13: J1.c12, U11.7 (A5)
/AB14: J1.a11, U11.8 (A6)
/AB15: J1.c11, U11.9 (A7)
/CLOCK: U4.1 (CLK), X1.8 (OUT)
/D0: U1.33 (D0), U2.11 (Q0), U3.11 (D0), U6.9 (D7), U7.11 (Q0), U8.2 (A0)
/D1: U1.32 (D1), U2.12 (Q1), U3.12 (D1), U6.8 (D6), U7.12 (Q1), U8.3 (A1)
/D2: U1.31 (D2), U2.13 (Q2), U3.13 (D2), U6.7 (D5), U7.13 (Q2), U8.4 (A2)
/D3: U1.30 (D3), U2.15 (Q3), U3.15 (D3), U6.6 (D4), U7.15 (Q3), U8.5 (A3)
/D4: U1.29 (D4), U2.16 (Q4), U3.16 (D4), U6.5 (D3), U7.16 (Q4), U8.6 (A4)
/D5: U1.28 (D5), U2.17 (Q5), U3.17 (D5), U6.4 (D2), U7.17 (Q5), U8.7 (A5)
/D6: U1.27 (D6), U2.18 (Q6), U3.18 (D6), U6.3 (D1), U7.18 (Q6), U8.8 (A6)
/D7: U1.26 (D7), U2.19 (Q7), U3.19 (D7), U6.2 (D0), U7.19 (Q7), U8.9 (A7)
/DB0: J1.a5, U8.18 (B0)
/DB1: J1.c5, U8.17 (B1)
/DB2: J1.a4, U8.16 (B2)
/DB3: J1.c4, U8.15 (B3)
/DB4: J1.a3, U8.14 (B4)
/DB5: J1.c3, U8.13 (B5)
/DB6: J1.a2, U8.12 (B6)
/DB7: J1.c2, U8.11 (B7)
/GPIO00_O0: D1.2 (A), J11.9, U6.12 (Q7)
/GPIO00_O1: D2.2 (A), J11.8, U6.13 (Q6)
/GPIO00_O2: D3.2 (A), J11.7, U6.14 (Q5)
/GPIO00_O3: D4.2 (A), J11.6, U6.15 (Q4)
/GPIO00_O4: D5.2 (A), J11.5, U6.16 (Q3)
/GPIO00_O5: D6.2 (A), J11.4, U6.17 (Q2)
/GPIO00_O6: D7.2 (A), J11.3, U6.18 (Q1)
/GPIO00_O7: D8.2 (A), J11.2, U6.19 (Q0)
/PLD_I1: J10.2, U4.3 (I1)
/PLD_O0: J1.c9, U4.23 (O0)
/RES: J1.c31, U9.5 (RST)
/R/~W: U1.34 (R/~W), U4.2 (I0)
/SYS_CLK: J1.a7, U1.37 (ϕ0), U4.15 (O8), U9.7 (~ST)
/~CS_RAM0: D10.1 (K), U2.20 (~CS), U4.20 (O3)
/~CS_RAM1: D11.1 (K), U4.19 (O4), U7.20 (~CS)
/~CS_ROM: D9.1 (K), U3.20 (~CE), U4.18 (O5)
/~IOEN_00_GPIO0: J1.a28, U5.15 (O0), U6.11 (Cp)
/~IOEN_01: J1.c28, U5.14 (O1)
/~IOEN_02_UART: J1.a27, U5.13 (O2)
/~IOEN_03: J1.c27, U5.12 (O3)
/~IOEN_04: J1.a26, U5.11 (O4)
/~IOEN_05: J1.c26, U5.10 (O5)
/~IOEN_06: J1.a25, U5.9 (O6)
/~IOEN_07: J1.c25, U5.7 (O7)
/~IOEN_08: J1.a24, U12.15 (O0)
/~IOEN_09: J1.c24, U12.14 (O1)
/~IOEN_10: J1.a23, U12.13 (O2)
/~IOEN_11: J1.c23, U12.12 (O3)
/~IOEN_12: J1.a22, U12.11 (O4)
/~IOEN_13: J1.c22, U12.10 (O5)
/~IOEN_14: J1.a21, U12.9 (O6)
/~IOEN_15: J1.c21, U12.7 (O7)
/~IO_RD_DIR: J1.c8, U4.16 (O7), U8.1 (A->B)
/~IO_SEL: J1.a8, U4.17 (O6), U5.4 (E1), U12.4 (E1)
/~IRQ: J1.c30, R5.2, U1.4 (~IRQ)
/~NMI: J1.a30, R3.2, U1.6 (~NMI)
/~PLD_O9: J1.c7, U4.14 (O9)
/~QOE: U2.22 (~OE), U3.22 (~OE), U4.21 (O2), U7.22 (~OE)
/~QWE_RAM: D12.1 (K), U2.27 (~WE), U4.22 (O1), U7.27 (~WE)
/~RES: D13.1 (K), J1.a31, R4.2, U1.40 (~RES), U9.6 (~RST)
GND: C1.2, C2.2, C3.2, C4.2, C5.2, C6.2, C7.2, C8.2, C9.2, C10.2, C11.2, C12.2, C13.2, C14.2, C15.2, H1.1, H2.1, J1.c1, J1.c6, J1.c10, J1.c19, J1.c29, J1.c32, J9.1, J10.1, J11.1, RN1.5 (R4.2), RN1.6 (R3.2), RN1.7 (R2.2), RN1.8 (R1.2), RN2.5 (R4.2), RN2.6 (R3.2), RN2.7 (R2.2), RN2.8 (R1.2), SW1.2, SW2.4 (A), U1.21 (VSS), U2.14 (GND), U3.14 (GND), U4.12 (GND), U5.8 (GND), U6.1 (OE), U6.10 (GND), U7.14 (GND), U8.10 (GND), U8.19 (CE), U9.4 (GND), U10.1 (A->B), U10.10 (GND), U10.19 (CE), U11.1 (A->B), U11.10 (GND), U11.19 (CE), U12.5 (E2), U12.8 (GND), X1.7 (GND)
unnamed: D1.1 (K), RN1.3 (R3.1)
unnamed: D2.1 (K), RN1.2 (R2.1)
unnamed: D3.1 (K), RN1.1 (R1.1)
unnamed: D4.1 (K), RN1.4 (R4.1)
unnamed: D5.1 (K), RN2.1 (R1.1)
unnamed: D6.1 (K), RN2.4 (R4.1)
unnamed: D7.1 (K), RN2.3 (R3.1)
unnamed: D8.1 (K), RN2.2 (R2.1)
unnamed: D9.2 (A), RN3.2 (R2.1)
unnamed: D10.2 (A), RN3.4 (R4.1)
unnamed: D11.2 (A), RN3.3 (R3.1)
unnamed: D12.2 (A), RN3.1 (R1.1)
unnamed: D13.2 (A), R2.1
unnamed: J6.1, SW2.2 (B)
unnamed: J6.2, SW2.5 (B)
unnamed: J9.2, U4.13 (~OE)
unnamed: R1.1, SW1.1, U9.1 (~PB_RST)
VCC: C1.1, C2.1, C3.1, C4.1, C5.1, C6.1, C7.1, C8.1, C9.1, C10.1, C11.1, C12.1, C13.1, C14.1, C15.1, J1.a1, J1.a6, J1.a10, J1.a19, J1.a29, J1.a32, J9.3, J10.3, R1.2, R2.2, R3.1, R4.1, R5.1, RN3.5 (R4.2), RN3.6 (R3.2), RN3.7 (R2.2), RN3.8 (R1.2), SW2.1 (A), U1.2 (RDY), U1.8 (VDD), U1.36 (BE), U2.28 (VCC), U3.28 (VCC), U4.24 (VCC), U5.6 (E3), U5.16 (VCC), U6.20 (VCC), U7.28 (VCC), U8.20 (VCC), U9.3 (TOL), U9.8 (VCC), U10.20 (VCC), U11.20 (VCC), U12.16 (VCC), X1.11 (Vcc), X1.14 (Vcc)

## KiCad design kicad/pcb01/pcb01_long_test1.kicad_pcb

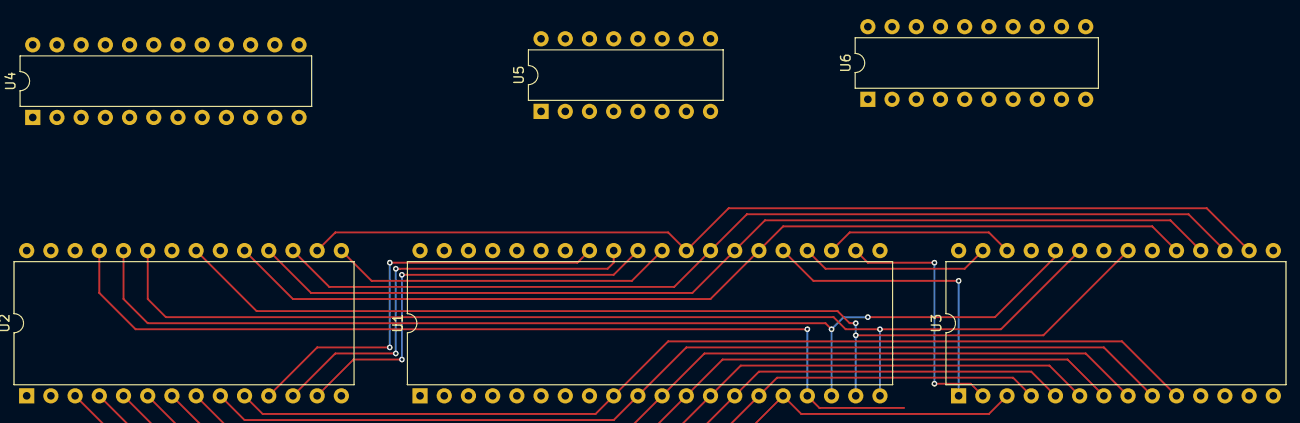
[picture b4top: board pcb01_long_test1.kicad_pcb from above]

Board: 2 copper layers, 6 parts (0 on the bottom side), 32 nets.

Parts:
U1: W65C02SxP; DIP-40_W15.24mm
U2: HM62256BLP; DIP-28_W15.24mm
U3: 27C512; DIP-28_W15.24mm
U4: PAL20RS10; DIP-24_W7.62mm
U5: 74LS138; DIP-16_W7.62mm
U6: 74HCT574; DIP-20_W7.62mm

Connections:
/A0: U1.9 (A0), U2.10 (A0), U3.10 (A0)
/A1: U1.10 (A1), U2.9 (A1), U3.9 (A1)
/A2: U1.11 (A2), U2.8 (A2), U3.8 (A2)
/A3: U1.12 (A3), U2.7 (A3), U3.7 (A3)
/A4: U1.13 (A4), U2.6 (A4), U3.6 (A4)
/A5: U1.14 (A5), U2.5 (A5), U3.5 (A5)
/A6: U1.15 (A6), U2.4 (A6), U3.4 (A6)
/A7: U1.16 (A7), U2.3 (A7), U3.3 (A7)
/A8: U1.17 (A8), U2.25 (A8), U3.25 (A8)
/A9: U1.18 (A9), U2.24 (A9), U3.24 (A9)
/A10: U1.19 (A10), U2.21 (A10), U3.21 (A10)
/A11: U1.20 (A11), U2.23 (A11), U3.23 (A11)
/A12: U1.22 (A12), U2.2 (A12), U3.2 (A12)
/A13: U1.23 (A13), U2.26 (A13), U3.26 (A13)
/A14: U1.24 (A14), U2.1 (A14), U3.27 (A14)
/A15: U1.25 (A15), U3.1 (A15)
/CLOCK: U1.37 (ϕ0), U4.1 (CLK)
/CS_RAM: U2.20 (~CS), U4.15 (O8)
/CS_ROM: U3.20 (~CE), U4.14 (O9)
/D0: U1.33 (D0), U2.11 (Q0), U3.11 (D0)
/D1: U1.32 (D1), U2.12 (Q1), U3.12 (D1)
/D2: U1.31 (D2), U2.13 (Q2), U3.13 (D2)
/D3: U1.30 (D3), U2.15 (Q3), U3.15 (D3)
/D4: U1.29 (D4), U2.16 (Q4), U3.16 (D4)
/D5: U1.28 (D5), U2.17 (Q5), U3.17 (D5)
/D6: U1.27 (D6), U2.18 (Q6), U3.18 (D6)
/D7: U1.26 (D7), U2.19 (Q7), U3.19 (D7)
/QOE: U2.22 (~OE), U3.22 (~OE), U4.17 (O6)
/QWE_RAM: U2.27 (~WE), U4.18 (O5)
/RWB: U1.34 (R/~W), U4.2 (I0)
GND: U1.21 (VSS), U2.14 (GND), U3.14 (GND), U4.12 (GND), U4.13 (~OE), U5.8 (GND), U6.10 (GND)
VCC: U1.2 (RDY), U1.4 (~IRQ), U1.6 (~NMI), U1.8 (VDD), U1.36 (BE), U2.28 (VCC), U3.28 (VCC), U4.24 (VCC), U5.16 (VCC), U6.20 (VCC)
